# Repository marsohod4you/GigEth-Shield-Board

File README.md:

# GigEth-Shield-Board
1G Ethernet Extension PCB for Marsohod3 / Marsohod2 / Marsohod3GW2 boards

PCB Board is based on Realtek RTL8211E PHY and released in KiCAD6.
Board can be installed on top of FPGA boards: 
 - Marsohod2
 - Marsohod2bis
 - Marsohod3
 - Marsohod3bis
 - Marsohod3GW2

Ext Board setup example:

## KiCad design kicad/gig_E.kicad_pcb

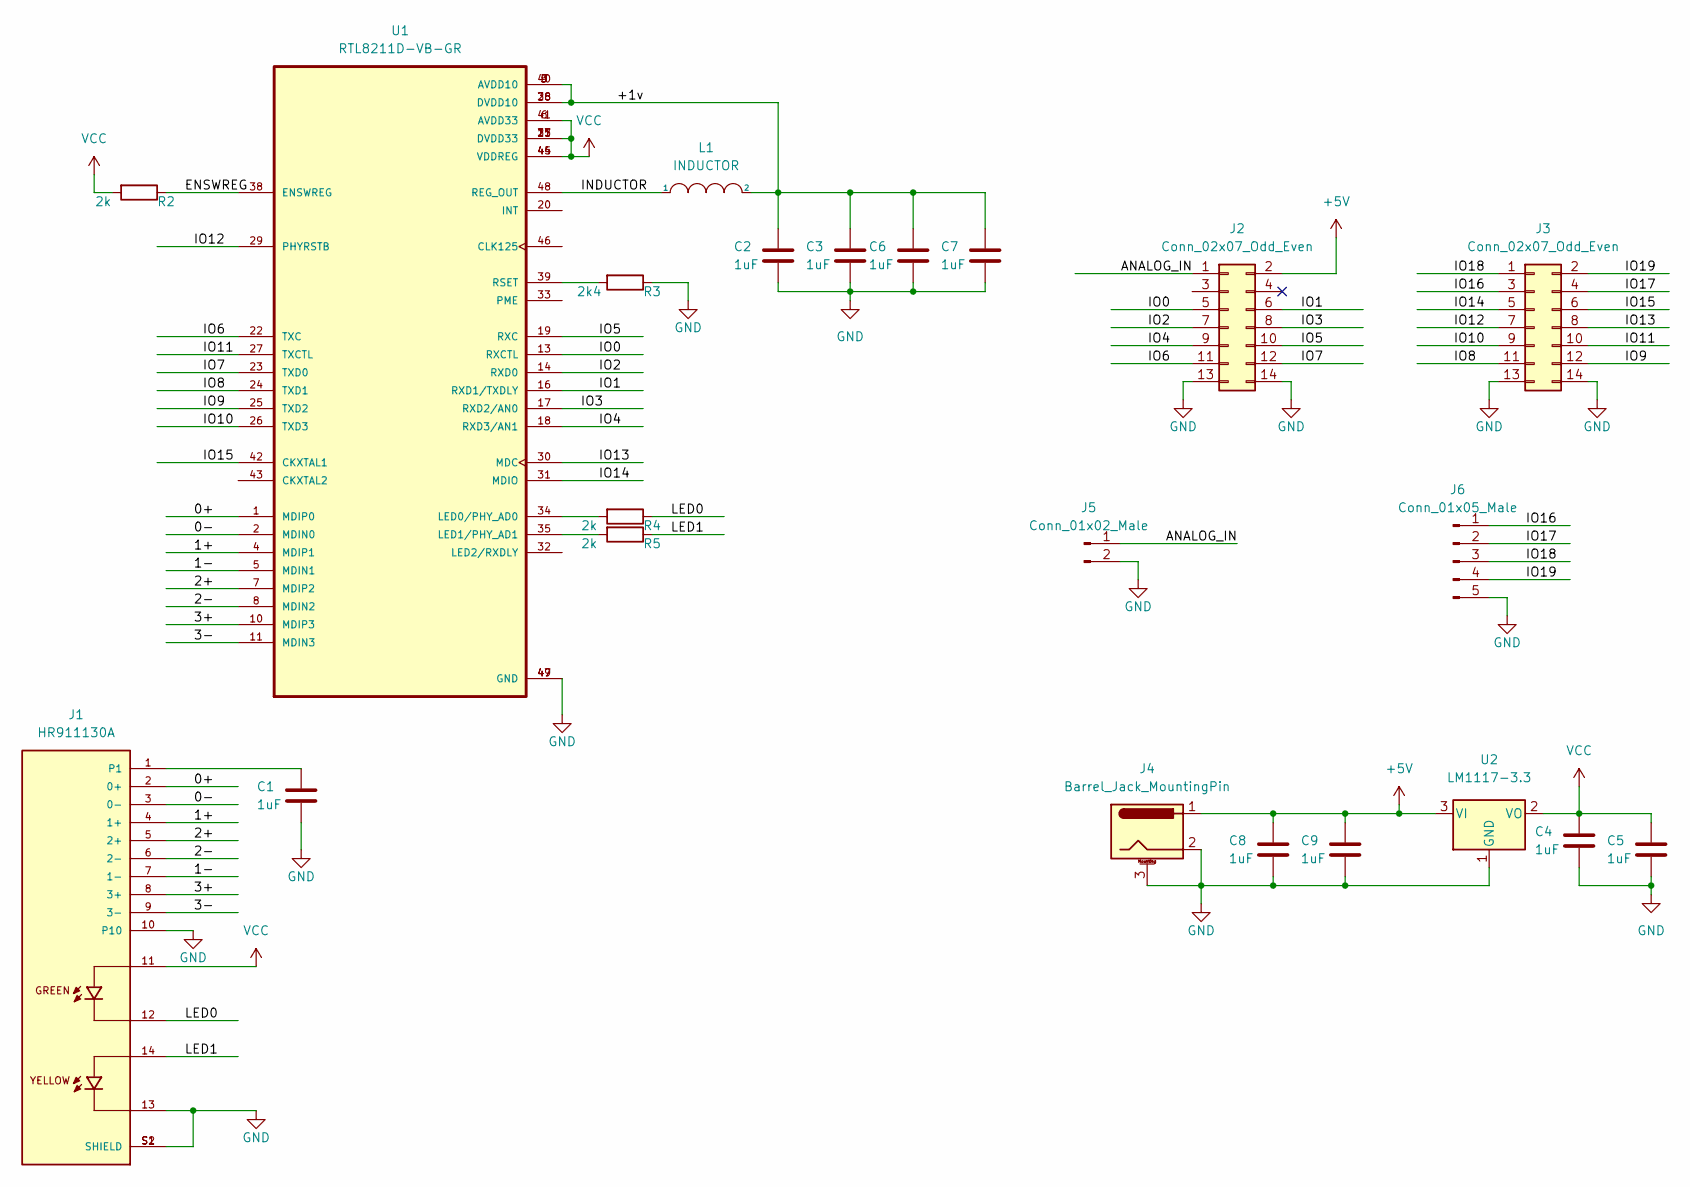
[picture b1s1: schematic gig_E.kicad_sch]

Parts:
C1, C2, C3, C4, C5, C6, C7, C8, C9: 1uF; C_0805_2012Metric_Pad1.18x1.45mm_HandSolder
J1: HR911130A; HANRUN_HR911130A; PARTREV A
J2, J3: Conn_02x07_Odd_Even; PinHeader_2x07_P2.54mm_Vertical
J4: Barrel_Jack_MountingPin; BarrelJack_CLIFF_FC681465S_SMT_Horizontal
J5: Conn_01x02_Male; PinHeader_1x02_P2.54mm_Vertical
J6: Conn_01x05_Male; PinHeader_1x05_P2.54mm_Vertical
L1: INDUCTOR; L_1812_4532Metric
R2, R4, R5: 2k; R_0805_2012Metric_Pad1.20x1.40mm_HandSolder
R3: 2k4; R_0805_2012Metric_Pad1.20x1.40mm_HandSolder
U1: RTL8211D-VB-GR; QFN-48-1EP_6x6mm_P0.4mm_EP4.3x4.3mm; PARTREV 1.2
U2: LM1117-3.3; SOT-223

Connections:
+5V: C8.1, C9.1, J2.2, J4.1, U2.3 (VI)
/0+: J1.2 (0+), U1.1 (MDIP0)
/0-: J1.3 (0-), U1.2 (MDIN0)
/1+: J1.4 (1+), U1.4 (MDIP1)
/1-: J1.7 (1-), U1.5 (MDIN1)
/2+: J1.5 (2+), U1.7 (MDIP2)
/2-: J1.6 (2-), U1.8 (MDIN2)
/3+: J1.8 (3+), U1.10 (MDIP3)
/3-: J1.9 (3-), U1.11 (MDIN3)
/+1v: C2.1, C3.1, C6.1, C7.1, L1.2, U1.3 (AVDD10), U1.9 (AVDD10), U1.28 (DVDD10), U1.36 (DVDD10), U1.40 (AVDD10)
/ANALOG_IN: J2.1, J5.1
/ENSWREG: R2.1, U1.38 (ENSWREG)
/INDUCTOR: L1.1, U1.48 (REG_OUT)
/IO0: J2.5, U1.13 (RXCTL)
/IO1: J2.6, U1.16 (RXD1/TXDLY)
/IO2: J2.7, U1.14 (RXD0)
/IO3: J2.8, U1.17 (RXD2/AN0)
/IO4: J2.9, U1.18 (RXD3/AN1)
/IO5: J2.10, U1.19 (RXC)
/IO6: J2.11, U1.22 (TXC)
/IO7: J2.12, U1.23 (TXD0)
/IO8: J3.11, U1.24 (TXD1)
/IO9: J3.12, U1.25 (TXD2)
/IO10: J3.9, U1.26 (TXD3)
/IO11: J3.10, U1.27 (TXCTL)
/IO12: J3.7, U1.29 (PHYRSTB)
/IO13: J3.8, U1.30 (MDC)
/IO14: J3.5, U1.31 (MDIO)
/IO15: J3.6, U1.42 (CKXTAL1)
/IO16: J3.3, J6.1
/IO17: J3.4, J6.2
/IO18: J3.1, J6.3
/IO19: J3.2, J6.4
/LED0: J1.12, R4.1
/LED1: J1.14, R5.1
GND: C1.2, C2.2, C3.2, C4.2, C5.2, C6.2, C7.2, C8.2, C9.2, J1.10, J1.13, J1.S1 (SHIELD), J1.S2 (SHIELD), J2.13, J2.14, J3.13, J3.14, J4.2, J4.3 (MountPin), J5.2, J6.5, R3.1, U1.47 (GND), U1.49 (GND), U2.1 (GND)
unnamed: C1.1, J1.1
unnamed: R3.2, U1.39 (RSET)
unnamed: R4.2, U1.34 (LED0/PHY_AD0)
unnamed: R5.2, U1.35 (LED1/PHY_AD1)
VCC: C4.1, C5.1, J1.11, R2.2, U1.6 (AVDD33), U1.15 (DVDD33), U1.21 (DVDD33), U1.37 (DVDD33), U1.41 (AVDD33), U1.44 (VDDREG), U1.45 (VDDREG), U2.2 (VO)

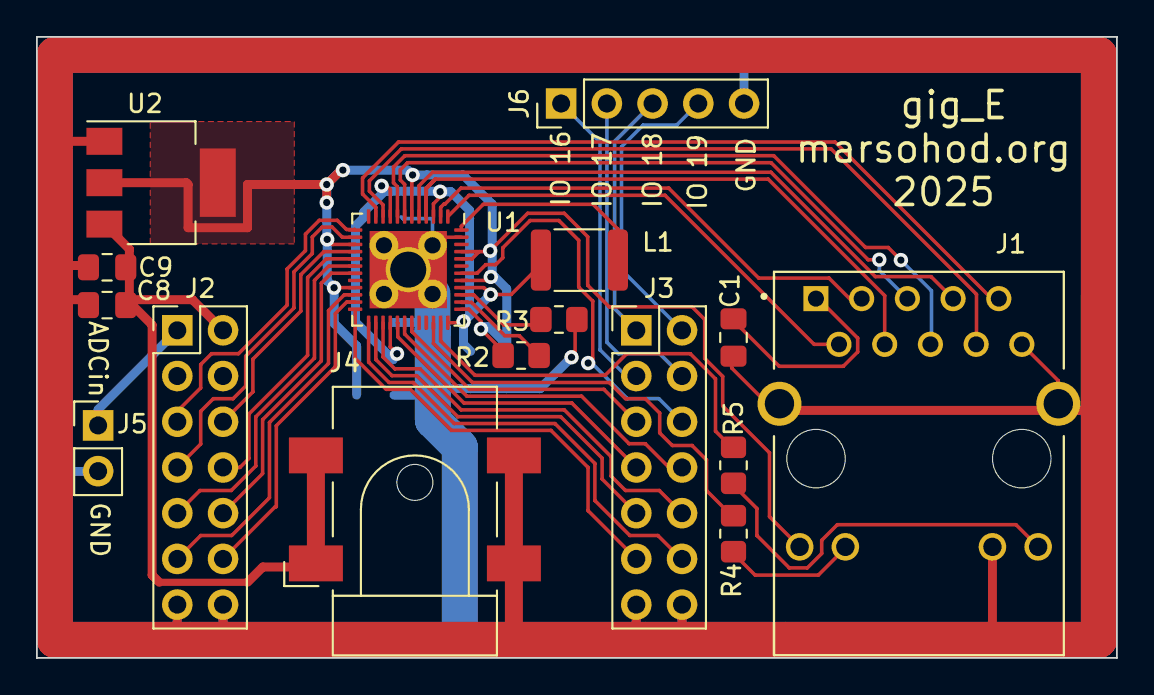
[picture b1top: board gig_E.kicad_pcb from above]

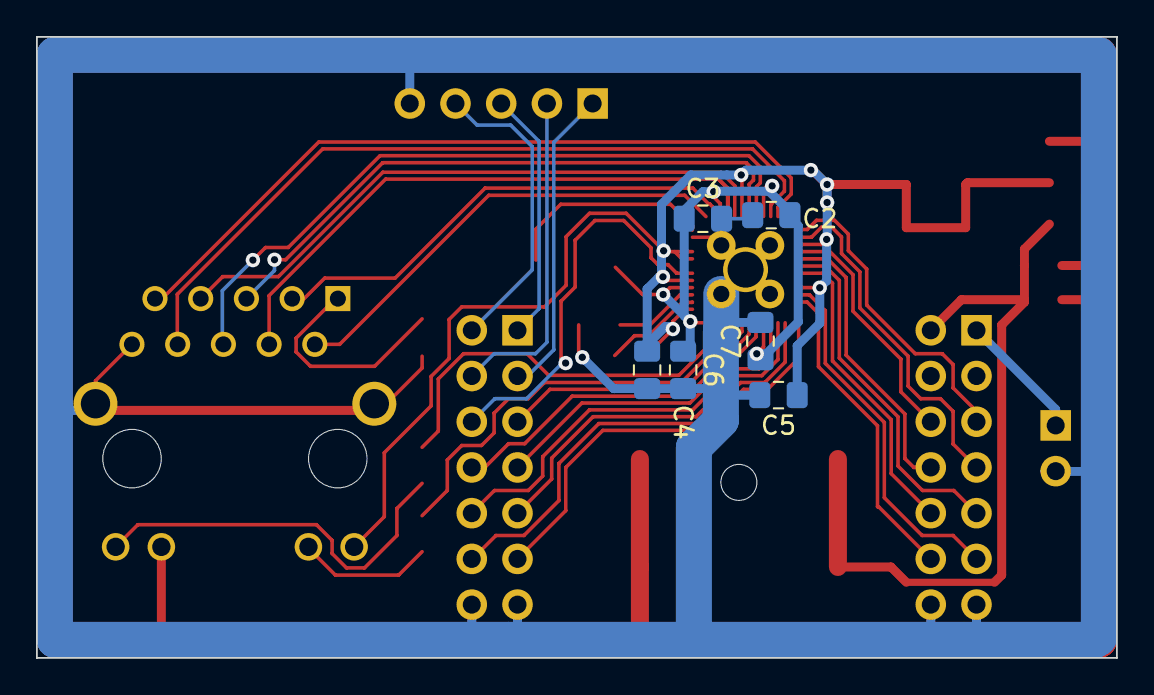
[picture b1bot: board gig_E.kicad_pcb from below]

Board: 2 copper layers, 60.0 x 34.5 mm, 22 parts (6 on the bottom side), 41 nets.

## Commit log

2025-04-23 Initial push of development files
2025-04-23 update readme file
2025-04-23 update photos
